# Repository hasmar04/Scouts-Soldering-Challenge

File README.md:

# Scouts-Soldering-Challenge

A soldering challenge suitable for Scouts all the way to Rovers.

As a member of the Australian Scouting movement, the logo has been used within this design for the purpose of promoting the movement, and to help the project to the target audience of Scouting members. 

For more information and/or assistance with implementing this challenge in your own Scout group, contact me at [246328@scoutsqld.com.au](mailto:246328@scoutsqld.com.au) 

### For more information on the Australian Scouting Movement, visit https://scouts.com.au

## Components Required
- 1x PCB (see 'pcb' folder)
- 2x Red LED
- 1x Green LED
- 1x Yellow LED
- 1x Orange LED
- 5x 330 ohm resistor
- 1x 10k ohm resistor
- 1x 6x6mm push button
- 1x Arduino Nano

More information can be found in the [Procurement Guide](https://github.com/hasmar04/Scouts-Soldering-Challenge/blob/main/docs/Procurement%20Guide.md)

## Documentation
Documentation can be found in the [/docs](<https://github.com/hasmar04/Scouts-Soldering-Challenge/tree/main/docs>) folder. This includes:
- Arduino IDE Installation and Getting Started
- Arduino Programming Fundamentals
- Procurement Guide
- Assembly Guide

## Contributing
If there is anything that you think is missing from this repository, or you find an error, please [create an issue](<https://github.com/hasmar04/Scouts-Soldering-Challenge/issues>) or fix it yourself and create a pull request.

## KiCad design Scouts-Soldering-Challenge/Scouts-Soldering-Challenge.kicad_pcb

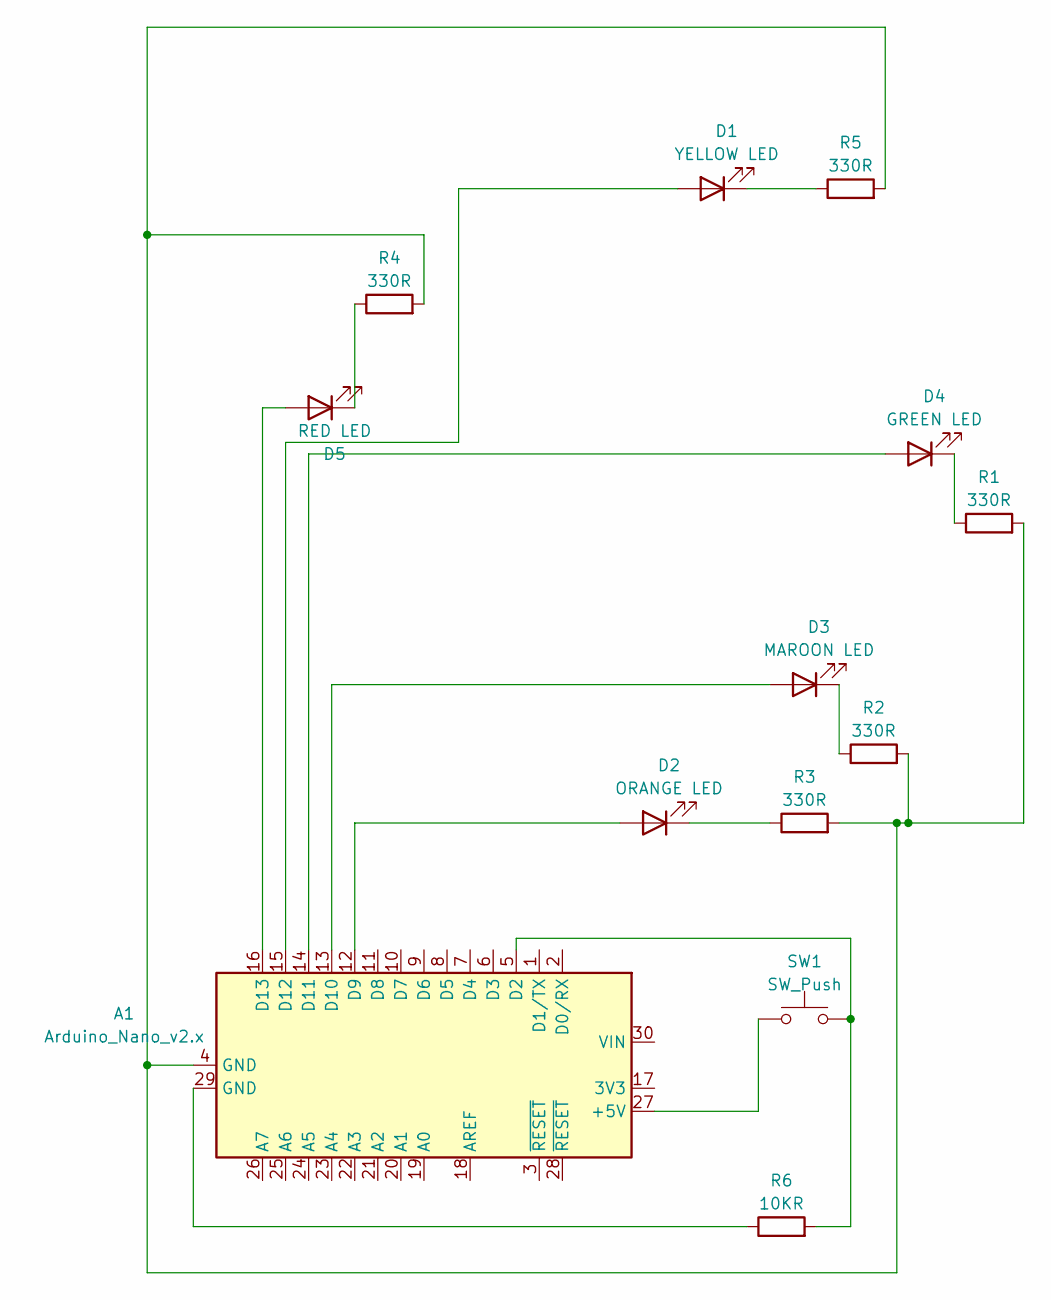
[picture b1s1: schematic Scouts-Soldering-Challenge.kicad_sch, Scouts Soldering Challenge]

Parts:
A1: Arduino_Nano_v2.x; Arduino_Nano
D1: YELLOW LED; LED_D3.0mm
D2: ORANGE LED; LED_D3.0mm
D3: MAROON LED; LED_D3.0mm
D4: GREEN LED; LED_D3.0mm
D5: RED LED; LED_D3.0mm
R1, R2, R3, R4, R5: 330R; R_Axial_DIN0207_L6.3mm_D2.5mm_P10.16mm_Horizontal
R6: 10KR; R_Axial_DIN0207_L6.3mm_D2.5mm_P10.16mm_Horizontal
SW1: SW_Push; SW_PUSH_6mm

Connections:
unnamed: A1.27 (+5V), SW1.1
unnamed: A1.5 (D2), R6.2, SW1.2
unnamed: A1.12 (D9), D2.2 (A)
unnamed: A1.13 (D10), D3.2 (A)
unnamed: A1.14 (D11), D4.2 (A)
unnamed: A1.15 (D12), D1.2 (A)
unnamed: A1.16 (D13), D5.2 (A)
unnamed: A1.4 (GND), R1.2, R2.2, R3.2, R4.2, R5.2
unnamed: A1.29 (GND), R6.1
unnamed: D1.1 (K), R5.1
unnamed: D2.1 (K), R3.1
unnamed: D3.1 (K), R2.1
unnamed: D4.1 (K), R1.1
unnamed: D5.1 (K), R4.1

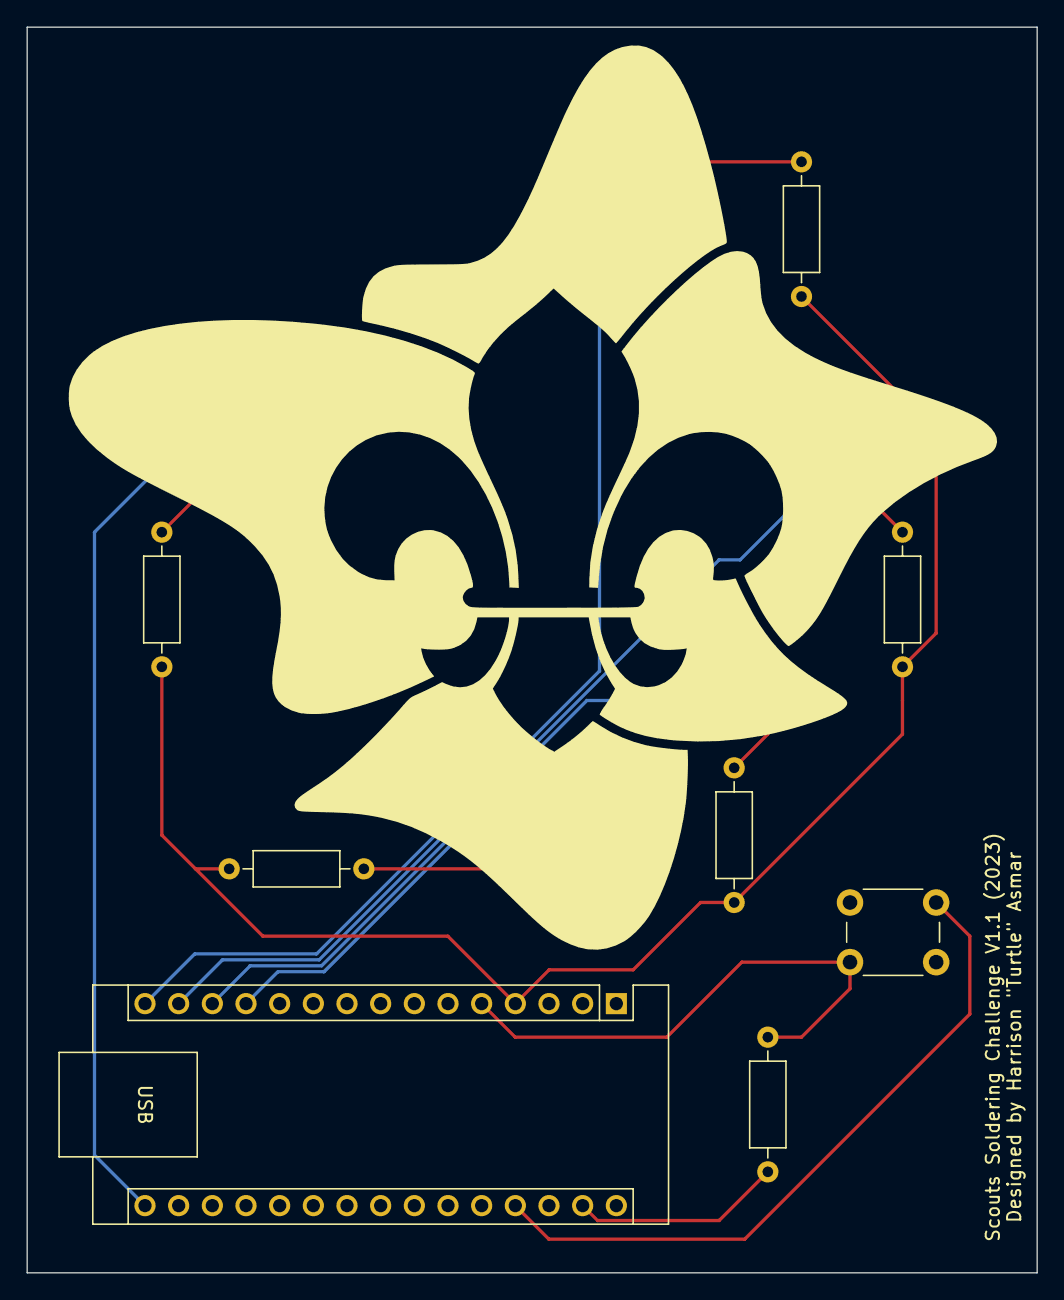
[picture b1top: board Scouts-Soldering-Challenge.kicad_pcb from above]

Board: 2 copper layers, 76.2 x 94.0 mm, 13 parts (0 on the bottom side), 14 nets.

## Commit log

2023-05-19 Updated README
    Added reference to Australian Scouting Movement, including a link
2023-05-19 Added PCBway exports to gitignore
    Prevents PCBway plugin archives from being uploaded to repo
2023-05-19 Added render of PCB V1.0
2023-05-19 Added logo png
    Cropped from original
2023-05-19 Created PCB and schematic
    Created schematic and two PCB designs, one larger but too expensive to make, and a smaller, more economical design. Both contain the same amount of parts.
2023-05-29 Added components required list
2023-05-29 Added word docs to gitignore
2023-05-29 Updated some trace routes
    Minor changes, still functionally the same
2023-06-02 Added *.ods to gitignore
2023-06-10 Created board test code
    Allows for testing of the button and all the LEDs at once. Also outputs to the Serial Monitor in case LEDs are not working.
2023-06-10 Corrected mistake in PCB
    Wiring is all still the same, but the pins on the LED were connected in the wrong orientation, meaning the PCB showed the LED rotated the wrong way.
2023-06-10 Rotated LEDs to adapt to updated schematic
    LEDs now have the correct leg connecting to the square ground pad. Old PCB design still works, but this is now in line with standard design principles.
2023-06-10 Bumped PCB Version to V1.1
2023-06-10 Fixed mistake of disconnected component
    In the process of correcting the schematic changes, I disconnected one of the LEDs and forgot to reconnect it. This has been rectified.
2023-06-10 Added image to README
    Added example assembled board image to README
2023-06-20 boardTest - Serial now prints on new lines
2023-06-20 Added libreoffice lock files to gitignore
2023-06-20 Create Arduino IDE Installation & Getting Started V1.0.pdf
    Brief guide on installing the IDE and testing that the Arduino is connected and all components are working.
2023-06-20 Updated boardTest
    Updated boardTest to make variable names match silkscreened values on PCB.
2023-06-21 Create Programming Fundamentals Cheatsheet
    Should help some participants to write their own code with less assistance.
2023-06-21 Renamed pcb files folder to /pcb
    Makes finding files easier, repository should make more sense in how it is laid out now.
2023-06-21 Update README - Contact details and required parts
    Added my contact email and the fact a PCB is required for the project.
2023-07-08 Creat contribution guide for Issue #3
    Adds a link to create an issue and the suggestion of a pull request for more experienced users.
2023-07-08 Moved docs to folder
    Created docs folder, moved documents there, and added link in README
2023-07-08 Created procurement guide
    Includes links to suggested components from Element14, and what to look for if sourcing elsewhere.
2023-07-08 Converted some docs to markdown
    Converted the Arduino Programming Fundamentals and Procurement Guide to markdown, allows for easier code contribution by others without needing two separate documents in the repository.
    Did not convert Arduino IDE guide as it contains many images and would take too long to convert, and it should never need many updates.
2023-07-08 Updated README
    Updated README to reflect conversion of some docs from PDF to Markdown
2023-07-08 Added link to procurement guide in README
2023-07-08 Fixed README link to procurement guide
    Sadly the previous link did not work.
2023-07-13 Updated contact email
    Removed personal email and replaced with new Scouts Qld email
